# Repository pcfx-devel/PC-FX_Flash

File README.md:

# PC-FX_Flash

This is a design of a non-volatile backup memory board for the PC-FX. It's based on the
FX-BMP, but doesn't need batteries, and manages savegames by group, rather than by individual game.

## Design

I designed the board using the free version of EAGLE, which is limited to 2 layers and
100mm x 100mm board size.  I have included the project files as well as the gerber outputs.

There are two boards in the repository - one for the DIP version of the Flash memory, and one
for the PLCC version of the Flash memory.  In both cases, the chips need to be soldered directly
to the board, as there isn't sufficient clearance for socketing.

## Assembly

I have included gerber files, as well as BOM.csv and assembly.csv files, for use with
JLCPCB's SMD assembly service, if you are interested in taking advantage of that.

For the DIP version of the board, the assumption is that you would solder the chip yourself, although
some of the capacitors are 0402 size, which may not be easy to handle yourself...

For the PLCC version of the board, the files are also included for JLCPCB to assemble for you, but
the Flash memory devices aren't always in stock. However, as I write this, they are both available
and inexpensive at distributors like Mouser and Digikey, and this board is designed for easy handling
for somebody ready to assemble a simple surface-mount board. If this is your desire, I suggest getting
a stencil made, using solder paste made for stencil use, and heating with any of: reflow oven,
reflow hotplate, or hot air soldering station.

## Case

You can also find the design for a case/enclosure, courtesy of Jeff Chen (Twitter: @jeffqchen).
This is suitable for any 3D printer; I particularly liked the resin prints I ordered online.
The case is designed to accept M2-12 socket-head screws and nuts.

## Circuit Design Concepts

As the PC-FX uses a 5V bus, all chips need to be 5V-compliant.

In order to drive the chip-select (low), a 3-input OR gate is used, requiring the following
lines to ALL be low in order to trigger the chip select:
 1. Cartridge select (keys in on range 0xE8000000 - 0xEFFFFFFF)
 2. A25 (narrows the range to 0xE8000000 - 0xEBFFFFFF)
 3. A24 (narrows the range to 0xE8000000 - 0xE9FFFFFF)

**NOTE:**\
The address lines are numbered according to the chip's address lines, which are not
necessarily the same as the CPU's address lines. The second byte on the memory chip is
actually memory address 0xE8000002, so the memory chip's A0 is effectively the CPU's A1).

## Software

### Program Overview

The overall idea of this software is to store multiple "slots" of the entire internal savegame memory
into the Flash cart, and manage them. Since the Flash cart is 512KB and the internal savegame memory
is 32KB, this leaves room for roughly 12 slots, after deducting space for comments and the program
which manages all this.

When saving memory into a slot, you will be prompted for the date and a shhort comment (in future,
this comment may be expanded). This is to help jog your memory of when this save was made (or what
is important about the contents), for retrieval at a later date.

When examining the contents of the cart, you will be presented with the date and comment for each slot,
and will be able to list what games have saves inside of the area - but no fine-grained management
is either programmed or planned.

### Development Chain & Tools

This was written using a version of gcc for V810 processor, with 'pcfxtools' which assist in
building executables for PC-FX, and 'liberis' which is a library of functions targetting the PC-FX.

These can be found here:\
\
\

### Development Status
This code uses both 'C' and assembler code, and may also be used as a demonstration of how to program
using several of the facilities of the PC-FX. During the development of this management utility,
several issues have been discovered and fixed in liberis, and one compiler/linker issue remains
outstanding at this time... so this program should still be considered as 'beta'.

### Flashing the Cart

At the moment, this program is being tested via the pcfx_uploader development tool
, but
will soon be able to be programmed into the card as an auto-boot cartridge (once testing
has completed). I also plan to create utilities for programming cartridges and self-booting
images as part of this (but they don't exist as yet).

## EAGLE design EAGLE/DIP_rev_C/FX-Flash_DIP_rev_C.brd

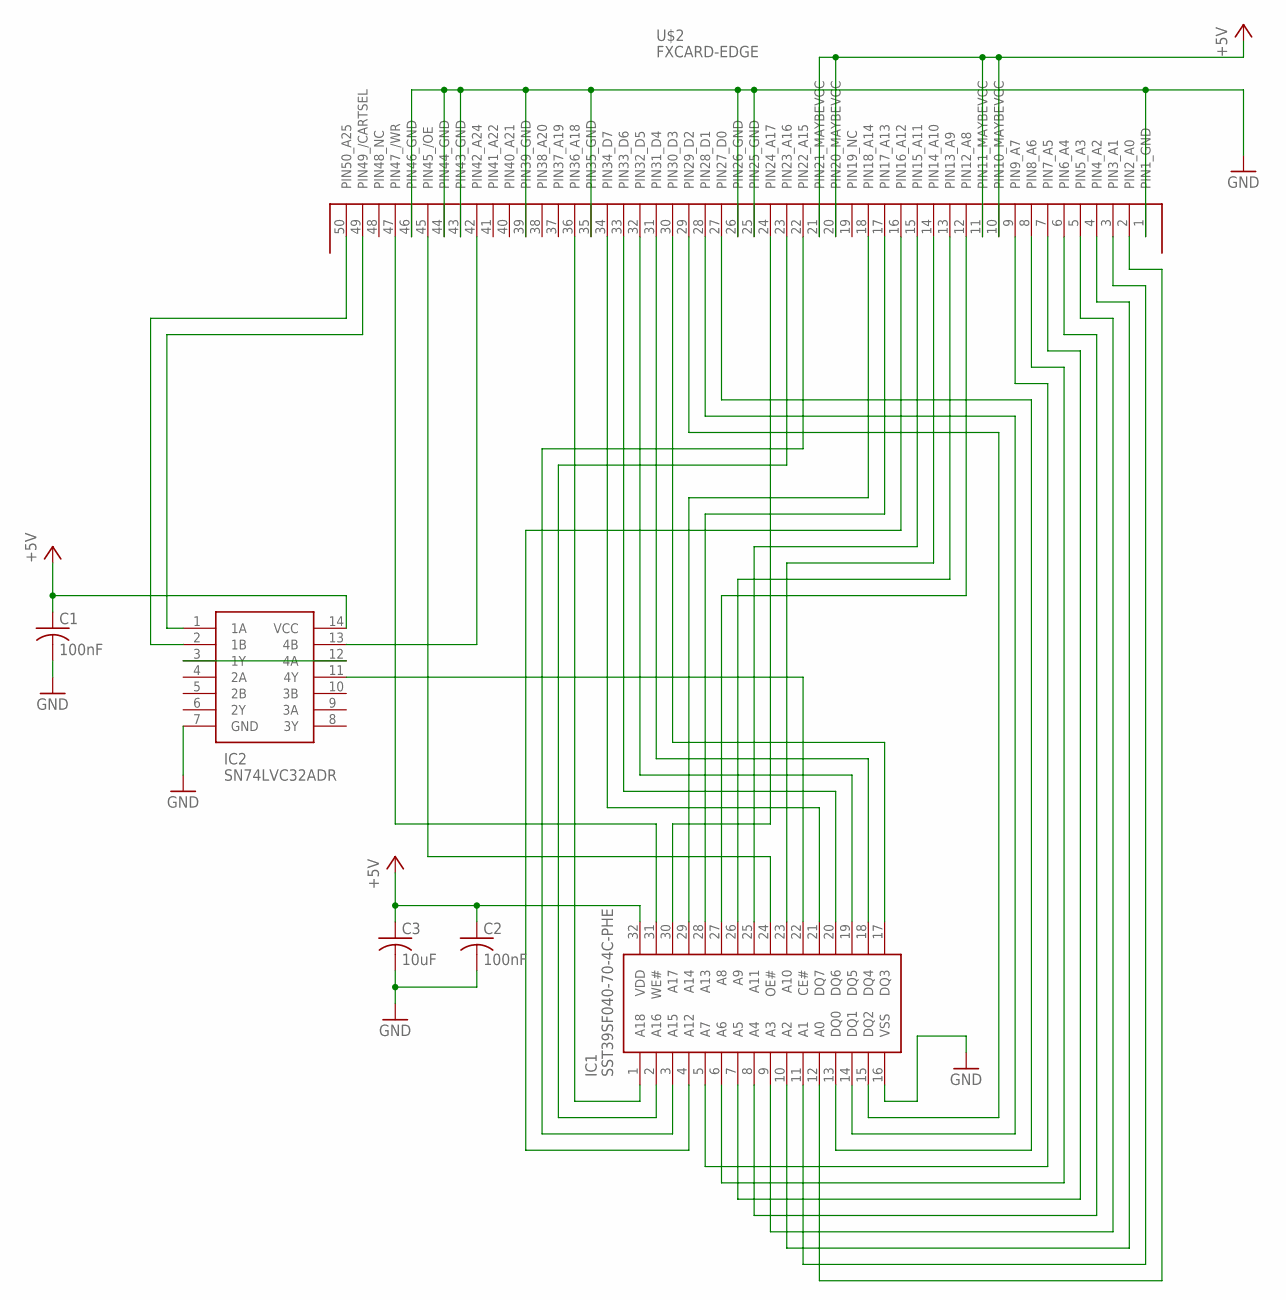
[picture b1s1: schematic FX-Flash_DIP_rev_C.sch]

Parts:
C1, C2: 100nF; C0805
C3: 10uF; C0805
IC1: SST39SF040-70-4C-PHE; DIP1556W56P254L4191H508Q32N
IC2: SN74LVC32ADR; SOIC127P600X175-14N
U$2: FXCARD-EDGE

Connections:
+5V: C1.1, C2.1, C3.1, IC1.32 (VDD), IC2.14 (VCC), U$2.10 (PIN10_MAYBEVCC), U$2.11 (PIN11_MAYBEVCC), U$2.20 (PIN20_MAYBEVCC), U$2.21 (PIN21_MAYBEVCC)
GND: C1.2, C2.2, C3.2, IC1.16 (VSS), IC2.7 (GND), U$2.1 (PIN1_GND), U$2.25 (PIN25_GND), U$2.26 (PIN26_GND), U$2.35 (PIN35_GND), U$2.39 (PIN39_GND), U$2.43 (PIN43_GND), U$2.44 (PIN44_GND), U$2.46 (PIN46_GND)
unnamed: IC1.18 (DQ4), U$2.31 (PIN31_D4)
unnamed: IC1.17 (DQ3), U$2.30 (PIN30_D3)
unnamed: IC2.13 (4B), U$2.42 (PIN42_A24)
unnamed: IC2.3 (1Y), IC2.12 (4A)
unnamed: IC1.22 (CE#), IC2.11 (4Y)
unnamed: IC1.31 (WE#), U$2.47 (PIN47_/WR)
unnamed: IC1.24 (OE#), U$2.45 (PIN45_/OE)
unnamed: IC1.1 (A18), U$2.36 (PIN36_A18)
unnamed: IC1.30 (A17), U$2.24 (PIN24_A17)
unnamed: IC1.2 (A16), U$2.23 (PIN23_A16)
unnamed: IC1.3 (A15), U$2.22 (PIN22_A15)
unnamed: IC1.29 (A14), U$2.18 (PIN18_A14)
unnamed: IC1.28 (A13), U$2.17 (PIN17_A13)
unnamed: IC1.4 (A12), U$2.16 (PIN16_A12)
unnamed: IC1.25 (A11), U$2.15 (PIN15_A11)
unnamed: IC1.23 (A10), U$2.14 (PIN14_A10)
unnamed: IC1.21 (DQ7), U$2.34 (PIN34_D7)
unnamed: IC1.20 (DQ6), U$2.33 (PIN33_D6)
unnamed: IC1.19 (DQ5), U$2.32 (PIN32_D5)
unnamed: IC1.26 (A9), U$2.13 (PIN13_A9)
unnamed: IC1.27 (A8), U$2.12 (PIN12_A8)
unnamed: IC2.2 (1B), U$2.50 (PIN50_A25)
unnamed: IC2.1 (1A), U$2.49 (PIN49_/CARTSEL)
unnamed: IC1.15 (DQ2), U$2.29 (PIN29_D2)
unnamed: IC1.14 (DQ1), U$2.28 (PIN28_D1)
unnamed: IC1.13 (DQ0), U$2.27 (PIN27_D0)
unnamed: IC1.5 (A7), U$2.9 (PIN9_A7)
unnamed: IC1.6 (A6), U$2.8 (PIN8_A6)
unnamed: IC1.7 (A5), U$2.7 (PIN7_A5)
unnamed: IC1.8 (A4), U$2.6 (PIN6_A4)
unnamed: IC1.9 (A3), U$2.5 (PIN5_A3)
unnamed: IC1.10 (A2), U$2.4 (PIN4_A2)
unnamed: IC1.11 (A1), U$2.3 (PIN3_A1)
unnamed: IC1.12 (A0), U$2.2 (PIN2_A0)

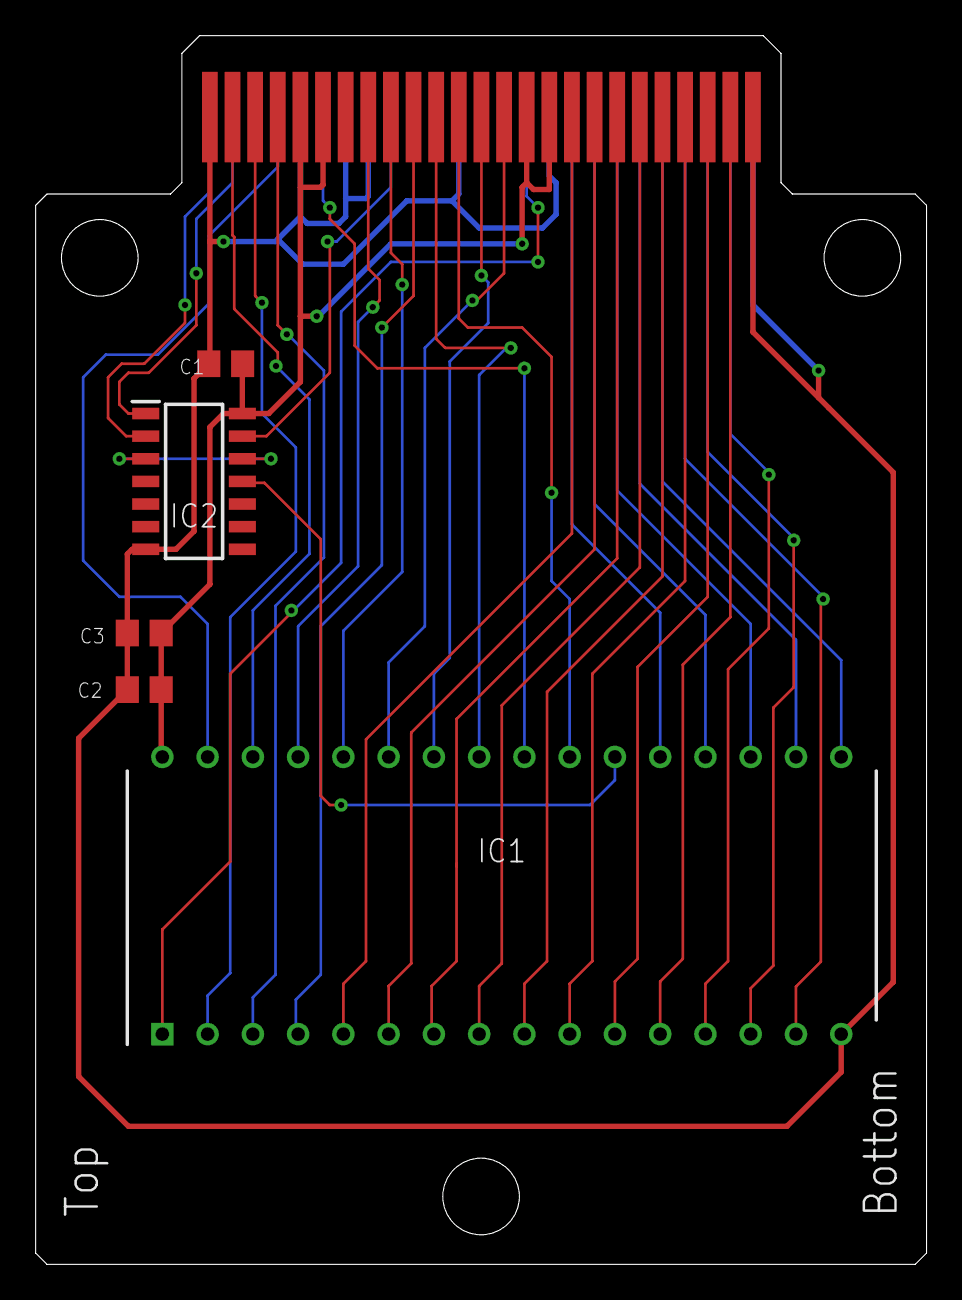
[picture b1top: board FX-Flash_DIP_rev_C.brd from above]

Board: 2 copper layers, 50.0 x 69.0 mm, 6 parts (0 on the bottom side), 36 nets.

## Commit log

2023-01-08 Initial Build
2023-01-08 Check Flash chip_id and expand comment size
2023-01-08 Add 'secret' erase menu; workaround unaligned problems caused by outstanding compiler issue
2023-01-08 Pre-fetch info on bank menu to speed up scrolling
2023-01-08 Re-arrange folder structure to accommodate flash programmer later
2023-01-09 clean comments
2023-01-09 Initial check-in
    Rough initial version of programmer. Expectation was that fx_uploader would send data to a known location, and this would access that... however, liberis clears out all of memory, so that doesn't wor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
    A hacked binary of this version does work however; it does need some way of loading the binary payload data though.
2023-01-22 Compile with new v810-ld linker, and add flashboot maker script
2023-03-19 update gitignore
2023-03-19 Deploy embedded binary
    This update allows the flash programmer to deploy whatever binary is in the "payload" file, and prompts the user with the description found in "payload_name" (up to 31 characters).
2023-03-19 Release code (deploy FX Megavault program to FX-Flash carts)
2023-05-02 Update DIP design to use 0805 capacitors for easy soldering (rev C)

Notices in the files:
EAGLE/DIP_rev_C/FX-Flash_DIP_rev_C.brd:
(c) 2023
